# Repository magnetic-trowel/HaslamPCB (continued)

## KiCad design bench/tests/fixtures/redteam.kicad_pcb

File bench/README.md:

# haslambench

Benchmark harness for automated and LLM-driven KiCad placement and routing. It
fetches real boards from a manifest, turns them into route and place tasks, runs a
method (an "adapter") on each task k times, and scores every attempt by re-opening
the saved board with `kicad-cli` under the board's own rules. Design rationale:
[docs/topics/verification/harness.md](../docs/topics/verification/harness.md).

## Setup (Ubuntu 22.04/24.04)

```bash
git clone https://github.com/magnetic-trowel/HaslamPCB
cd HaslamPCB
bench/scripts/setup.sh          # KiCad 10 (PPA, no recommends), bench/.venv (and upstream Freerouting 2.5.0, explicit use only)
                                # --all: also the fork below, haslam/.venv and the synth venv (README.md Part 1)
                                # --dry-run: print the installs, write env.sh only (bench/tests/test_setup.py)
tools/research/routing/install_freerouting_fork.sh $(grep -v '^#' bench/freerouting.ref) --pin   # the Freerouting fork, pinned: the control
source bench/.venv/bin/activate
haslambench doctor              # --pipeline: also the design pipeline (venvs, KiCad libraries, env.sh)
```

The control's fork ref lives in one file, `bench/freerouting.ref`; it moves with the weekly baseline tag
([experiment-tiers](../docs/topics/verification/experiment-tiers.md)). The installer builds with one Gradle worker (Maven
Central answers parallel fetches with 429) and exits non-zero with the reason when the build fails.

**Without sudo** the same script still works:
- KiCad runs from the official `kicad/kicad:10.0.7` image, unpacked into `~/.cache/haslambench` (~2.5 GB). It needs no root and no `/dev/fuse`.
- It uses an installed Apptainer or Singularity. Without one, it installs Apptainer 1.5.4 rootless into `~/.cache/haslambench/apptainer` (~160 MB) with Apptainer's own `install-unprivileged.sh`, which unpacks EL8 RPMs. Python stand-ins replace `rpm2cpio` and `cpio` if they are missing.
- The rootless install needs x86_64 and unprivileged user namespaces. Check with `unshare -Ur true && echo ok`. Ubuntu 22.04 allows them by default; 24.04 blocks them unless an admin relaxes `kernel.apparmor_restrict_unprivileged_userns`.
- If `python3-venv` is missing, the venv comes from `uv`.
- Freerouting, the venv and `env.sh` all live in your home directory. Set `HASLAM_HOME` to put the large files on another disk.
- `source bench/.venv/bin/activate` picks up the KiCad wrapper. Force this route with `--kicad container`.
- The container sees `$HOME`, `/tmp` and the current directory. For a `--workdir` elsewhere, export `APPTAINER_BIND=/that/path`.

Other OSes or setups: point `HASLAM_KICAD_CLI` / `HASLAM_KICAD_PYTHON` at KiCad 10. Both accept a command with a wrapper, e.g. `flatpak run --command=kicad-cli org.kicad.KiCad`, or use `HASLAM_KICAD_WRAP` as a prefix for both. The container set-up points `HASLAM_KICAD_WRAP` at `kicad-exec`, which shows KiCad only the CPUs a job may use (`HASLAM_KICAD_THREADS`, else the queue's `HASLAMQ_CPUS`, else `nproc`; `HASLAM_KICAD_THREADS=0` turns the cap off): KiCad otherwise starts one thread per CPU on the machine. The Python must be able to `import pcbnew`. Freerouting is the build named by `HASLAM_FREEROUTING` (a binary or JAR; the JAR needs Java 25), else the one pinned in `$HASLAM_HOME/haslam-freerouting.pin` (the magnetic-trowel fork, the same pin the bridge uses); with neither, runs stop with an error. Nothing picks the newest install. Run `pytest bench/tests` to check the install.

## Usage

```bash
M=bench/manifests/candidates.jsonl
haslambench fetch   -m $M -j 8                 # download boards at pinned commits (verifies sha256)
haslambench prepare -m $M -j 8                 # convert to KiCad 10, qualify, build route/place tasks
haslambench run --adapter reference --kinds route,place --probe freerouting -j 8 --name human
haslambench run --adapter freerouting -k 1 --timeout 900 -j 8 --name fr-fork      # the pinned fork; deterministic: one attempt
haslambench report haslam-work/results/human haslam-work/results/fr-fork
```

Everything lives under `--workdir` (default `./haslam-work`): `cache/` (fetched files),
`tasks/<id>/{reference,route,place,place-fixed}/` and `results/<run>/<adapter>/<kind>/<id>/attempt-N/`.
Runs resume: re-running with the same `--name` skips finished attempts.

Useful filters on `fetch`/`prepare`: `--tiers permissive`, `--tags rf,ddr`, `--only id1,id2`,
`--limit N`. On `run`: `--splits A,B` (A ≤ 31 pads, B ≤ 100, C larger), `--all` to include
boards whose human layout is not clean.

## Suites

`bench/suites/*.txt` are board-id lists for `--only @FILE`:
- `haslambench tasks --write-suite FILE` writes the boards that qualified on your KiCad version.
- `qualified-kicad-10.0.7.txt`: the 112 manifest boards that qualified on KiCad 10.0.7.
- `pcbworld-d3{a,b,c}-test.txt` are PCBWorld's D3 eval splits (99 / 10 / 10).

### Experiment-tier suites

How to run an experiment on them: [suites/README.md](suites/README.md).

Four lists for the [experiment tiers](../docs/topics/verification/experiment-tiers.md), plus `merit-213.txt` (the 213
merit boards, an archived regression set). Built by `python3 tools/haslamres/suites.py --tags DIR` (seed 20261120) on
2026-11-20 from the results index (100,968 runs), the board-tag suites and the corpus manifest; the same inputs give
the same lists. Rebuild monthly, with a new seed for the random part.

| suite | boards | 4+ layers | footprints, median (range) | CPU-h per method-run of all | boards with own history |
|---|---|---|---|---|---|
| `sprint-frontier` | 60 | 22 | 61 (14-257) | 14 | 60 |
| `sprint-quality` | 80 | 40 | 64 (17-149) | 26 | 24 |
| `ladder` | 300 | 154 | 80 (5-400) | 198 | 94 |
| `canary` | 28 | 20 | 476 (195-2056) | 30 | 22 |

- Shared rules: one board per owner (the account of the board's repository in the corpus manifest), and no owner
  shared between the two sprint suites and the ladder. Human-clean: tag `human_drc_errors.clean` and a prepared task
  whose human layout is clean and complete (`usable_with_reference`).
- `sprint-frontier`: 48 boards that responded in past two-arm A/Bs (open connections differed in at least a third of
  3+ board-seed pairs; mean 0.73), ranked by response per CPU-hour, at most 0.5 CPU-h per run and 400 footprints, a
  quarter with 4+ layers; plus 12 boards drawn at random from the same cost and footprint range. All have run as
  route and place tasks.
- `sprint-quality`: human-clean, 15-150 footprints, 2 or 4 layers, drawn evenly over the tags `pw_dcdc`,
  `pw_cell_buck`, `dec_rich`, `an_crystal` × layer count.
- `ladder`: human-clean, drawn evenly over six footprint bands (5-20, 21-50, 51-100, 101-150, 151-250, 251-400) ×
  (under 4 layers, 4+); 79 boards have over 150 footprints.
- `canary`: the 10 merit boards over 1,000 pads and the 18 human-clean boards over 400 footprints.
- CPU-h: the sum of each board's mean CPU-h per method-run in the index (corpus sweeps and the human reference left
  out); a board without history gets the mean of its footprint band. This mixes cheap and costly methods. At the
  rates of the restart-wrapped `s2-merit213` controls, one seed of `sprint-frontier` is about 54 CPU-h (bridge) or
  69 (staged place-and-route); `haslamres exp create` prints the estimate it uses.

### Mechanism suites and coverage

- `suites/mech/<name>.txt`: one list per mechanism and per standard kind of circuit (54: `bga` and its ball-count and pitch
  bands, `fine-pitch`, `diffpairs`, `buck`, `pours`, `usb`, ...), for experiments on that mechanism:
  [suites/mech/README.md](suites/mech/README.md). Built by `python3 tools/haslamres/mechsuites.py --tags DIR`.
- [suites/COVERAGE.md](suites/COVERAGE.md): per kind, the usable boards, human-clean boards and owners in the corpus and
  the kind's boards in each suite, by size and layer count; the holes. Built by `python3 tools/haslamres/coverage.py --tags DIR`,
  which also writes `sprint-quality-additions.txt` and `ladder-additions.txt`: boards of kinds the two suites held
  too few of. They are separate lists; the original suites are unchanged.

### Reproducing PCBWorld's routing baseline

PCBWorld's D3 boards are PCBench boards run through PCBWorld's own chain: KiCad 5→9.0.8 conversion, DRC repair, guide generation. Build them with that chain, then import them:

```bash
# in a PCBWorld checkout (https://github.com/LGAI-Research/PCBWorld); builds its KiCad engine
export PCBWORLD_DATA_ROOT=$PWD/var/datasets
bash tools/quickstart/prepare_pcbench.sh --workers 16
# back in this repo
haslambench --workdir haslam-d3 prepare-dir --dir $PCBWORLD_DATA_ROOT/pcbench/exacad_sorted \
  --board-glob processed_v9_guide_v3.kicad_pcb --only @bench/suites/pcbworld-d3a-test.txt --kinds route -j 16
HASLAM_FREEROUTING=<a Freerouting release> haslambench --workdir haslam-d3 run --adapter freerouting --passes 10 -k 5 -j 16 --name fr-release-mp10
```

PCBWorld published Freerouting 2.1.0 `-mp 10` at 0.80 (D3-A) and 0.78 (D3-B) clean-pass @5. Our scoring re-saves boards with KiCad 10 and uses each board's own severities. Expect close but not identical numbers; report both.

## Adapters

| Adapter | What it does |
|---|---|
| `reference` | The human layout: original copper (route) or original placement (place) |
| `noop` | Returns the task input unchanged (lower bound) |
| `freerouting` | Specctra DSN → the pinned Freerouting (the fork, our control; `-mt 1`, analytics off, per-attempt pass schedule, neck-down off, board edge/hole clearances passed, DSN widths clamped to the board minimum) → SES with placement block stripped → import |
| `freerouting-stock` | Same round trip with Freerouting's default settings; for explicit, deliberate use only (stock 2.5.0 is no longer a control) |
| any name + `--command` | External tool; template placeholders `{input} {output} {workdir} {kind} {attempt} {timeout}` |

Example external router: `haslambench run --adapter myrouter --command "python my_router.py {input} {output}"`.
The tool reads `{input}` (a `.kicad_pcb` with its project files beside it) and writes `{output}`.

**Sandbox.** `--command` methods run under bubblewrap (`bwrap`):
- no network;
- a private `/tmp` and `/var/tmp`;
- a home directory that shows only the haslambench tool cache (`HASLAM_HOME`), the current directory and any `--sandbox-ro PATH`;
- the workdir's tasks and results hidden, plus anything in `HASLAM_SANDBOX_HIDE` (colon-separated);
- only the attempt's own work directory writable.

A method can't read the human layout it is scored against, download it, or touch other attempts. On timeout the whole sandbox is killed. `--sandbox-net` allows network access, for LLM methods. `--no-sandbox` turns the sandbox off; the report then marks those attempts as unsandboxed.

## Scoring

- **Rebuilt board, reference rules, fresh process.** The scorer never judges the file a method wrote. It rebuilds the board from the task input plus only the changes the task allows:
  - route: the tracks, arcs and vias, copied as KiCad's own re-save of them, plus (score v10) the copper zones the method adds, unfilled, and each pad's own zone connection (`zone_connect`);
  - place: each unlocked footprint's position, rotation and side.

  The rebuilt board gets the reference `.kicad_pro`/`.kicad_dru`, zones are refilled, and `kicad-cli pcb drc` runs. Edits to rules, outline, keepouts, the task's zones, other pad properties, layers or nets can't change a score. Rules files a method writes are never read: the output is opened next to the task's own project files.
  - Teardrops, groups and tuning patterns are part of the routing. They are stripped from task inputs and are not transplanted or scored.
- **Integrity (`valid`).** Anything else the method changed is still detected, by comparing KiCad re-saves of output and input with the allowed changes normalized away (`foreign` lists them). Such a result is invalid.
  - Route results must keep placement, pad nets and every other board object, and route only on the board's copper layers and nets.
  - **Added zones** (route, joint and joint-fixed tasks, score v10). A method may pour copper. Each added zone must be a copper zone (no rule area or keepout) on the board's enabled copper layers, on a net the task has (no new nets, no net-less zones), inside the board's outer outline (10 µm slack for arcs), clear of rule areas that forbid pours on its layers, at a priority different from every zone it overlaps on a shared layer (KiCad 10.0.7's filler deadlocks on overlapping zones of different nets tied on priority and uuid), and with a unique uuid. Violations make the result invalid (`integrity.zones`, reasons in `zone_problems`). The task's own zones must stay exactly as given. These checks look at zone outlines; DRC checks the refilled copper (clearances, edge clearance, `items_not_allowed` in keepouts). Fills a method writes are ignored: DRC refills every zone, and the uncapped unconnected count fills them too, at start and end alike. Give new zones explicit pad-connection settings (clearance, thermal gap, spoke width) rather than relying on board defaults. No count or area cap; refilling many zones counts against `HASLAM_DRC_TIMEOUT` like anything else. In joint tasks the placement half ignores added zones and pads' zone connection (placement legality is judged on the placement alone); the routing half transplants and checks them onto that placement as in a route task.
  - Place results must keep pad nets and every non-pose property, leave anchored footprints where they are (locked ones, and ones carrying Edge.Cuts, which are part of the board outline), and not add or remove footprints or copper.
- **Copy check.** `copy` reports how much of the output reproduces the human layout exactly: tracks to 1 µm, or poses to 1 µm and 0.01°; and `copy.zones`, added zones whose outline overlaps a human zone on the same net and a shared layer with IoU ≥ 0.8. `suspect_copy` flags at least 20 tracks and 60% matching, at least 5 parts and 50%, or any copied zone. It is report-only until calibrated on real methods. The sandbox is the enforcement.
- **Route metrics.**
  - `clean`: valid, 0 unconnected, 0 error-level DRC violations. Severities come from the board's own project; library-environment checks are excluded.
  - `completion`: share of start-of-task unconnected items now routed.
  - `wl_ratio`: track length relative to the human layout.
  - `via_delta`: via count minus the human layout's.
- **Place metrics.**
  - `legal`: valid, no courtyard, clearance, edge-clearance, hole or keepout errors, and no footprint with more pad centres outside the board outline than the same footprint has in the human placement. Edge connectors may overhang as far as the designer's do.
  - `hpwl_ratio` relative to the human placement.
  - With `--probe freerouting`, the rebuilt placement is routed by a fixed router and scored like a route result, Cypress-style. An external router can be the probe: `--probe NAME --probe-command TEMPLATE` (or `probe=NAME,probe_command=TEMPLATE` in an `--arm`, without commas), run sandboxed as a route method.
- **Joint metrics** (`--kinds joint`: place and route in one output, from the place task's input).
  - The output's footprint poses are rebuilt into the place input. Placement integrity and `legal` are judged on that placement alone.
  - Its tracks and vias are then rebuilt onto that placement and scored like a route result.
  - Valid only if both parts are; `clean` also requires `legal`.
  - Baselines: `reference` (the human layout) and `human-freerouting` (Freerouting on the human placement).
- **Place-fixed tasks** (`--kinds place-fixed`, and `joint-fixed` for place and route from its input). A place task frees every unlocked footprint, the connectors and mounting holes too, so a placer can beat the human on wire length with a board that no longer fits its enclosure or cables. Place-fixed keeps the board's mechanical interface at the human pose, locked in the input, so it is scored exactly like a locked footprint (`locked_moved`); everything else is placed. Scoring and baselines are those of `place` and `joint`.
  - Fixed: connectors (USB, pin headers and sockets, JST/Molex/FPC/FFC, terminal blocks, barrel and audio jacks, RF, SD/SIM and card-edge slots, wire pads); mounting (screw holes, standoffs, fiducials, all-NPTH footprints); user-facing parts (switches, keyboard key switches such as Cherry MX, Kailh/Choc and Gateron, buttons, panel pots and encoders, displays, through-hole, light-pipe and LED-bar indicators, buzzers and speakers).
  - Free (the user's choices on borderline parts): programming and debug headers (JTAG, SWD, ISP/ICSP, PDI/UPDI, Tag-Connect, debug or prog in the name, value, description or reference, or a small header whose signal nets are one such interface), SMD LEDs, test points, jumpers and solder bridges (also pin headers with a jumper value), batteries and battery holders, trimmers, IC sockets; also net ties, heatsinks and plug-in modules. UART and display headers stay fixed.
  - The rules follow the placement research classifier (`haslam.place.fixed`); on the 112 qualified boards the two fix the same parts on 99 boards.
  - Rules, first match wins (`kicad_scripts/mech_rules.py` documents each, `rules_version` is recorded): exclusions; KiCad library (`Connector*`, `TerminalBlock*`, `MountingHole*`, `Fiducial*`, `Button_Switch*`, `Potentiometer*`, `Rotary_Encoder*`, `Display*`, `Buzzer_Beeper*`, `LED_THT`, connector makers); all pads NPTH; a THT LED name; a passive/diode/IC library, package name or reference (R, C, D, Q, ...) stops the rest; footprint-name patterns; KiCad symbol names as values (`Conn_01x04`, `SW_Push`); reference prefixes (J, P, H, MH, FID, SW, RV, ...) when the footprint fits. A connector that is a programming or debug header is then freed.
  - The task record lists every fixed part with its class and rule (`tasks["place-fixed"].fixed_mech`) and `movable`. `prepare --fixed-overrides FILE` takes `{"<board id>": {"fix": [refs], "free": [refs]}}` and records what it applied. Designer-locked parts and parts carrying Edge.Cuts stay anchored either way.
  - The human placement must also pass the place-fixed round trip. A board that fails it keeps its other tasks; runs skip only its place-fixed and joint-fixed tasks.
- **Degenerate place tasks.** Each place task records `movable`, the number of footprints a placer may move. A board whose parts are nearly all locked is trivially legal. `run --min-movable N` skips place, joint, place-fixed and joint-fixed tasks with fewer than N movable footprints (default 0: none are skipped).
- **Best-of-k** picks the attempt by clean, then completion, errors, track length (PCBWorld's best-potential @k). The report shows `cp1` (attempt 0) and `cpk`.
- **Rescoring.** After a scoring fix, `haslambench rescore RUN_DIR -j N` scores a run's saved outputs (and saved probe routes) again with the current scorer, without re-running the method. Each attempt records the version it was rescored from.
- **Versions.** Every attempt records `score_version` (now 10; v10 lets route and joint methods add zones and set pads' zone connection, and scores outputs without either exactly as v9). Tasks need task spec 5: locked footprints and footprints carrying Edge.Cuts stay in place, teardrops are stripped, repeated footprint uuids are made unique, and the human layout must pass the round trip. Place-fixed and joint-fixed need task spec 8 (classifier rules 4). From task spec 11 every task is limited to the copper layers the board uses (`kicad_scripts/layer_plan.py`); tasks of older specs must be prepared again. Re-run `prepare --force` on older task folders.
- **Red-team tests.** `bench/tests/test_redteam.py` runs cheating methods (move parts, delete a keepout, grow the outline, add a layer, shrink pads, swap nets, ship own rules, read or overwrite the reference, use the network) and requires each to be invalid, blocked or ineffective. Add a case for every new cheat found.

## Manifests

`bench/manifests/*.jsonl`, one board per line: `id`, `repo`, `commit` (40-hex),
`pcb_path`, `license` (required), plus `pcb_sha256`, `license_tier`, stats and
`tags`. Boards are never redistributed; only manifests are committed
(CDLA-Permissive-2.0).

- `candidates.jsonl`: the 297-board benchmark set.
- `wide.jsonl` (13,475) and `wide-noncommercial.jsonl` (843): the second sourcing pass,
  see [wide-board-corpus](../docs/topics/data/wide-board-corpus.md). Filter with
  `--tiers` and `--tags` (e.g. `--tags drc-clean`); `host-robots-restricted` marks rows on
  hosts whose robots.txt disallows raw/git paths.
- `pcb_path` may be an Eagle/Allegro `.brd`, Altium `.PcbDoc`, PADS `.asc` or CADSTAR `.cpa`;
  `fetch` converts it with `kicad-cli pcb import` and `pcb_sha256` stays the upstream hash.
- Rows with `archive_sha256` and `commit: null` are downloads (zip, tar or a single file),
  pinned by that hash.

## Known limitations

- KiCad 10 SES import deletes unlocked copper and applies placement. The adapter strips the SES placement block, and route tasks start without copper.
- Freerouting necks tracks down below the board's minimum width near fine-pitch pads and shrinks some to 75% to meet edge clearance; the `freerouting` adapter disables neck-down, but edge-driven shrinking remains (KiCad flags it as `track_width`).
- Freerouting has no seed flag, so best-of-k varies the pass count (`-mp` 10, 20, 30, ...).
- `inside` uses pad centres against the board outline. Courtyard-vs-edge overhang is not checked.

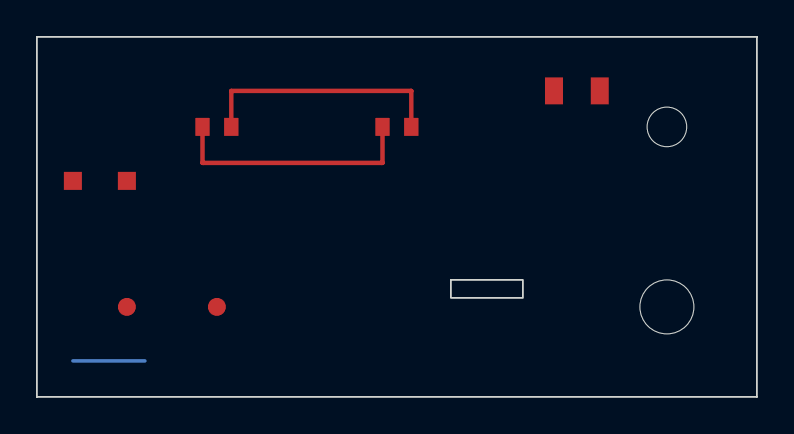
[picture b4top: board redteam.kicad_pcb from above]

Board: 2 copper layers, 40.0 x 20.0 mm, 9 parts (0 on the bottom side), 2 nets.

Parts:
H1: MH
H2: MountingHole; MountingHole_2.2mm_M2
J1: Conn_01x02; PinHeader_1x02_P2.54mm_Vertical
R1, R2: R
SL1: SLOT
SW1: SW_Push; SW_Push_Test
TP1, TP2: TP

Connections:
N1: R1.1, R2.1
N2: R1.2, R2.2

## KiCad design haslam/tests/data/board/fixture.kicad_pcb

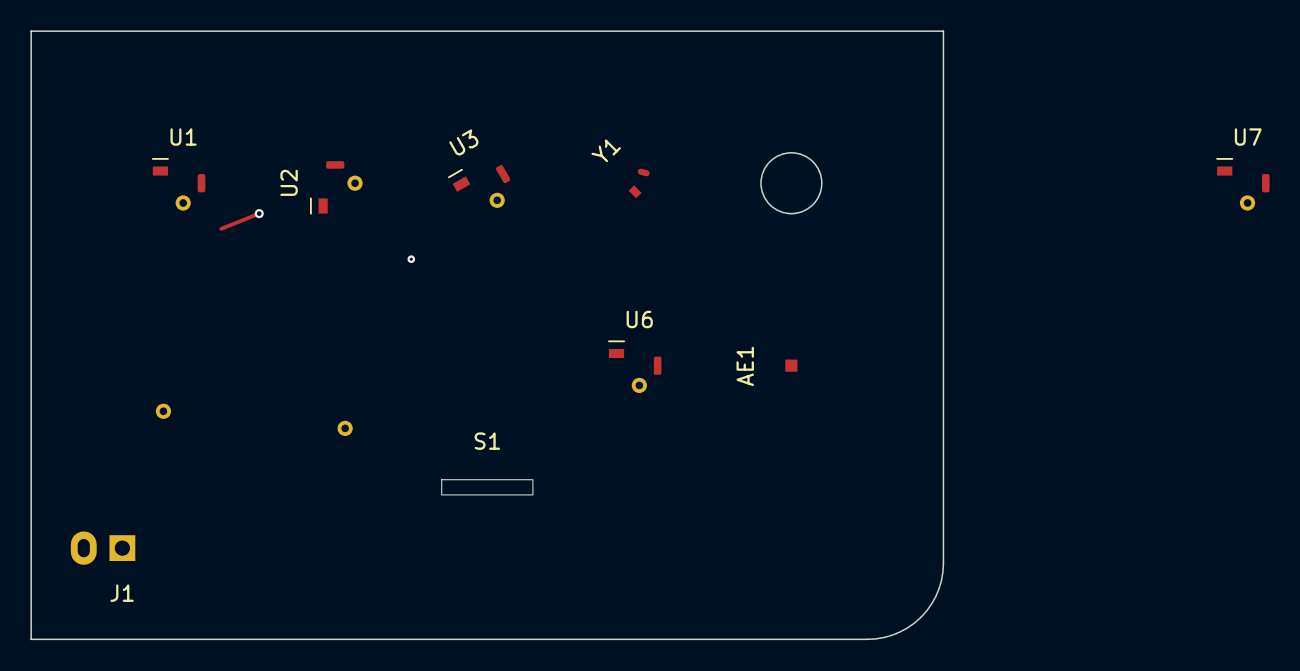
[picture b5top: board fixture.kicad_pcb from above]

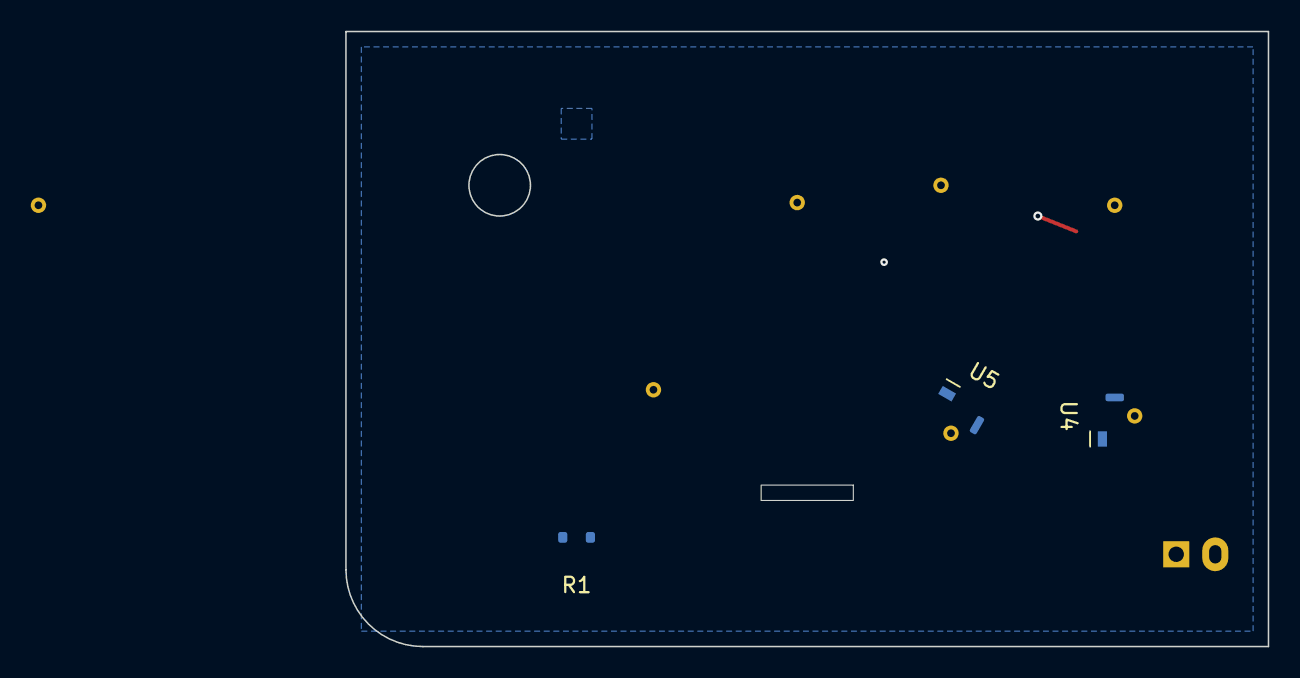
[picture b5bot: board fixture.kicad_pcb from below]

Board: 4 copper layers, 60.0 x 40.0 mm, 12 parts (3 on the bottom side), 5 nets.

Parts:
AE1: ANT
J1: CONN; THT2
R1: 10k; NOCRT
S1: SLOT
U1, U2, U3, U4, U5, U6, U7: ASYM; ASYM3
Y1: XTAL; ROUND

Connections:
GND: J1.2 (GND), R1.2, U1.2 (GND), U2.2 (GND), U3.2 (GND), U4.2 (GND), U5.2 (GND), U6.2 (GND), U7.2 (GND), Y1.2
SIG1: AE1.1, U1.1 (IN), U4.1 (IN), U7.1 (IN)
SIG2: U2.1 (IN), U5.1 (IN), Y1.1
SIG3: R1.1, U3.1 (IN), U6.1 (IN)
VCC: J1.1 (VCC), U1.3 (VDD), U3.3 (VDD), U4.3 (VDD), U5.3 (VDD), U6.3 (VDD), U7.3 (VDD)
